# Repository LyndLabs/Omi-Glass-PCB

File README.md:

# Omi Glass DevKit PCB
_This repo contains PCB design files & fab ready Gerbers for the Omi Glass DevKit._  

### About
Current Version: `R0.1-V3`  
Omi Glass DevKit is based around the ESP32-S3 & OV2640, adding image capture to the [Omi](https://omi.me) AI platform.  For modularity, we selected the [Xiao ESP32-S3 Sense](https://www.seeedstudio.com/XIAO-ESP32S3-Sense-p-5639.html?srsltid=AfmBOopCIzfd-8ibewO1jBZsJkmfUc-wzWkLOngDRXb3vafw_r4tShg3) microcontroller breakout.  It also has an onboard microphone & microSD reader.

### Ordering
**`R` indicates PCB revision # and `V` indicates the glasses version.**
- `/export` contains zipped gerber files, `BOM` component list, and `PNP` file for Pick and Place.
- board height must be `.8mm`
- `200K` resistors are recommended for voltage divider

### Changelog & Notes

`R0.0-Vx`
- `V2` glasses use `EVQPUL\C`, `V3` uses `EVQP7L\C` buttons to reduce size.
- `V2` production files not provided or recommended for production.
- `R0.0` designs contain minor issues that are rectified / bodged in production, `R0.1` files are provided for archive but were never fabricated.

`R0.2-V3` 
- switches back to `EVQPU` series buttons (bc Ro is fussy)
- delete jumper

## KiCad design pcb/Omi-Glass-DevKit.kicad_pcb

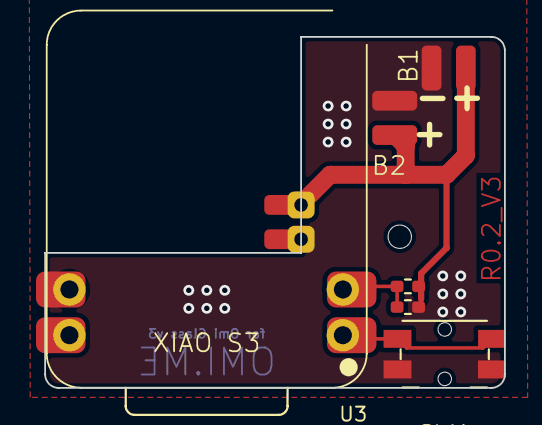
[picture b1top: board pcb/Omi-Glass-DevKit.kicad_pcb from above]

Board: 2 copper layers, 25.5 x 19.5 mm, 7 parts (1 on the bottom side), 4 nets.

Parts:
J1, J2, J3: Conn_01x02; JST_PH_S2B-PH-SM4-TB_1x02-1MP_P2.00mm_Horizontal
R1, R2: R_Small_US; R_0402_1005Metric_Pad0.72x0.64mm_HandSolder
SW1: SW_Push; Panasonic_EVQPUL_EVQPUC
U3: XIAO-ESP32S3-SMD

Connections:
GND: J1.1, J2.1, J3.2, R2.2, SW1.1, U3.13 (GND)
LOAD: J1.2, J2.2, J3.1, R1.1
MON: R1.2, R2.1, U3.2 (D1)
POWER: SW1.2, U3.1 (D0)

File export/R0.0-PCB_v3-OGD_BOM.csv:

Reference,Value,Footprint,Datasheet,Qty,DNP,Exclude from BOM,Exclude from Board
"R1,R2",R_Small_US,Resistor_SMD:R_0402_1005Metric,~,2,,,
SW1,SW_Push,Button_Switch_SMD:SW_SPST_EVQP7C,~,1,,,

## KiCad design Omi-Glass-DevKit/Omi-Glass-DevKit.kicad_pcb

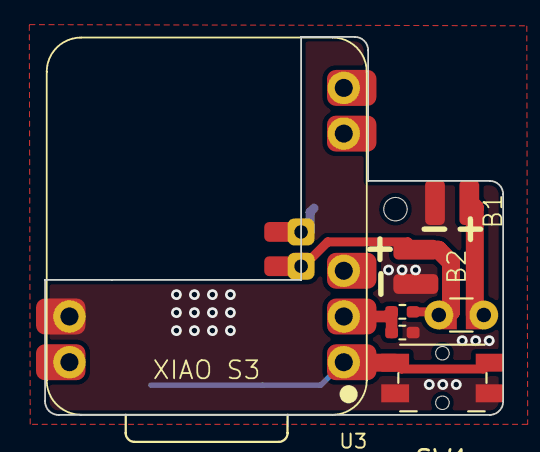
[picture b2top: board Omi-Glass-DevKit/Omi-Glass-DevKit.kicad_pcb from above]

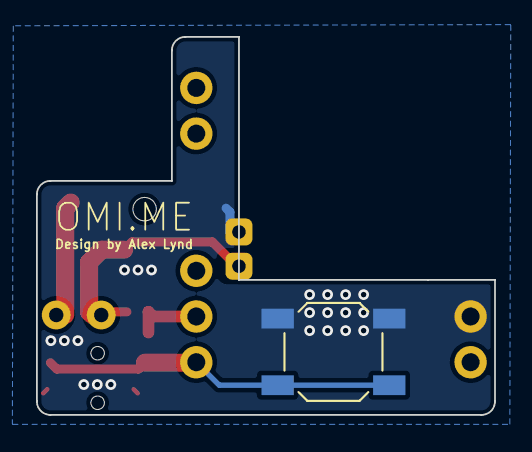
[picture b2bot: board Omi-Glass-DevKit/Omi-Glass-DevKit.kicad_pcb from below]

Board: 2 copper layers, 25.5 x 21.0 mm, 9 parts (2 on the bottom side), 5 nets.

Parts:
J1, J2, J2#2: Conn_01x02; JST_PH_S2B-PH-SM4-TB_1x02-1MP_P2.00mm_Horizontal
R1, R2: R_Small_US; R_0402_1005Metric_Pad0.72x0.64mm_HandSolder
SW1: SW_Push; Panasonic_EVQPUL_EVQPUC
SW1#2: SW_Push; SW_SPST_SKQG_WithStem
TH1: Thermistor_NTC; C_Disc_D3.0mm_W1.6mm_P2.50mm
U3: XIAO-ESP32S3-SMD

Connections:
GND: J1.1, J2.1, J2#2.1, R2.2, SW1.1, SW1#2.1, U3.13 (GND)
LOAD: J2.2, J2#2.2, R1.1, TH1.2, U3.16
MON: R1.2, R2.1, U3.2 (D1)
POWER: SW1.2, SW1#2.2, U3.1 (D0)
VBAT1: J1.2, TH1.1

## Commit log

2025-05-18 add v0.0 design files
2025-05-18 add v0.1 work
2025-05-18 add README changelog
2025-05-18 todo
2025-05-26 push R0.0 design for V3 glasses
2025-05-26 fix naming convention
2025-05-27 update production files
2025-05-27 bump file version to prevent confusion
2025-05-27 add old v2 render
2025-05-27 push updated V2 gerber
2025-05-28 bump to R0.2 V3
2025-05-28 move step
2025-05-28 update version on PCB copper
